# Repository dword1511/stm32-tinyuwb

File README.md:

# Tiny, Ultra-low-power UWB Localization Tag

This is a UWB localization tag based on Decawave `DWM1000` module and STMicro `STM32L031F6P6` ultra-low-power MCU.
The average power consumption is less than 5 mW in 6.8 Mbps mode (10 Hz update rate).

The tag has a built-in `LTC3588-1` energy harvester. WARNING: do not use `LTC3588-2`, their functionalities are very different!
The harvester can be left unpopulated and bypassed by connecting +3V3 directly to an external power source,
and then disabling the power-good logic in the source code.

## General Build Instructions

You will need the following packages (Debian/Ubuntu):

* build-essential
* gcc-arm-none-eabi
* git
* stlink-tools
* gdb-multiarch

You will have to flash and debug via the SWD test-points. Fine air-wire soldering skill required.

This project uses `libopencm3`. It will be automatically checked out during the building process.
To build the firmware, run `make`. To flash it, connect the board to a ST-Link, and then run `make flash`.
Alternatively, you can use `openocd` and any SWD debugger you fancy.

## Publication

This project was part of the following work. Please kindly consider citing the paper as shown:

```
@inproceedings{Capttery,
 author = {Zhang, Chi and Kumar, Sidharth and Bharadia, Dinesh},
 title = {{Capttery: Scalable Battery-like Room-level Wireless Power}},
 booktitle = {Proc. of ACM MobiSys},
 year = {2019},
}
```

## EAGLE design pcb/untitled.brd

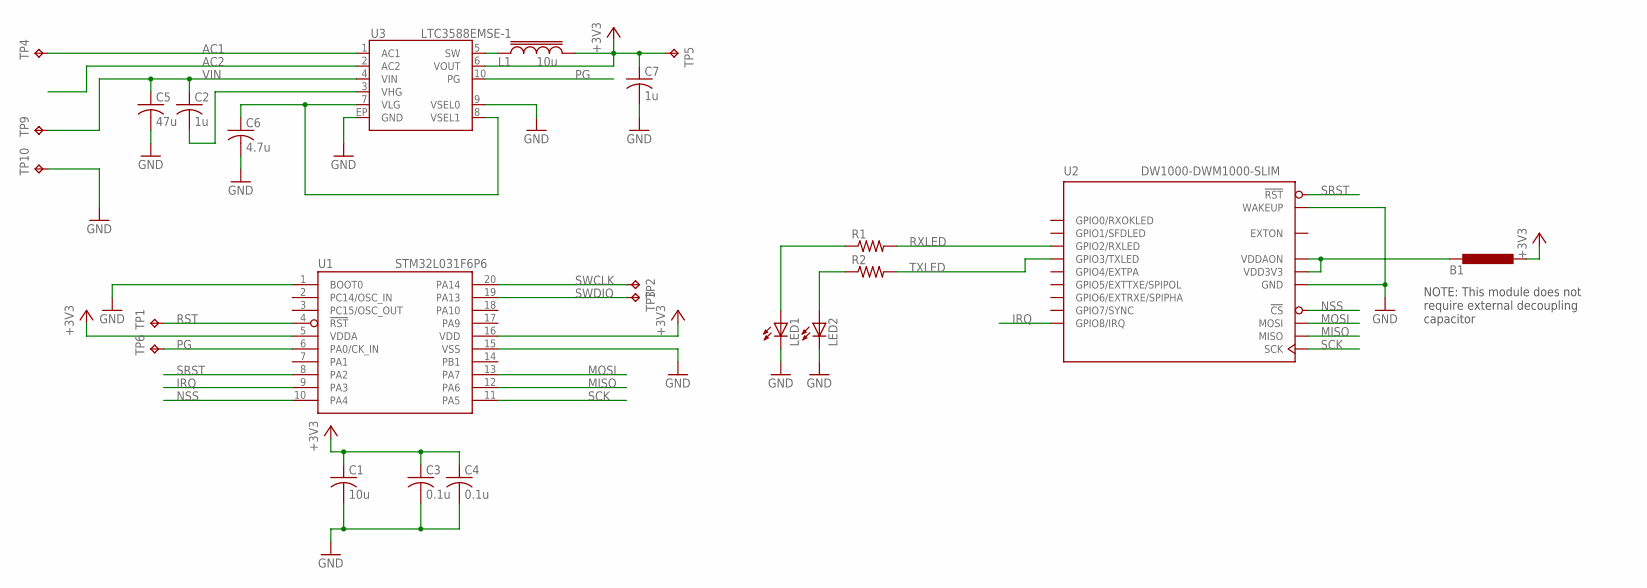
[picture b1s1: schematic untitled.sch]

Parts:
B1: BEAD-0603; 0603
C1: 10u; C0603
C2, C7: 1u; C0603
C3, C4: 0.1u; C0402
C5: 47u; C1206
C6: 4.7u; C0603
L1: 10u; 1008
LED1, LED2: LEDSML0603; SML0603
R1, R2: R-US_R0402; R0402
TP1, TP2, TP3, TP4, TP5, TP6, TP9, TP10: TPB1,27; B1,27
U1: STM32L031F6P6; TSSOP-20
U2: DW1000-DWM1000-SLIM
U3: LTC3588EMSE-1; MSOP-10-3X3-EP

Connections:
+3V3: B1.2, C1.1, C3.1, C4.1, C7.1, L1.2, TP5.TP, U1.5 (VDDA), U1.16 (VDD), U3.6 (VOUT)
AC1: TP4.TP, U3.1 (AC1)
AC2: U3.2 (AC2)
GND: C1.2, C3.2, C4.2, C5.2, C6.2, C7.2, LED1.C, LED2.C, TP10.TP, U1.1 (BOOT0), U1.15 (VSS), U2.2 (WAKEUP), U2.8 (GND), U2.16 (GND), U2.21 (GND), U2.23 (GND), U2.24 (GND), U3.9 (VSEL0), U3.EP (GND)
IRQ: U1.9 (PA3), U2.22 (GPIO8/IRQ)
MISO: U1.12 (PA6), U2.19 (MISO)
MOSI: U1.13 (PA7), U2.18 (MOSI)
unnamed: LED2.A, R2.1
unnamed: LED1.A, R1.1
unnamed: L1.1, U3.5 (SW)
unnamed: B1.1, U2.5 (VDDAON), U2.6 (VDD3V3), U2.7 (VDD3V3)
unnamed: C2.2, U3.3 (VHG)
unnamed: C6.1, U3.7 (VLG), U3.8 (VSEL1)
NSS: U1.10 (PA4), U2.17 (!CS)
PG: TP6.TP, U1.6 (PA0/CK_IN), U3.10 (PG)
RST: TP1.TP, U1.4 (!RST!)
RXLED: R1.2, U2.13 (GPIO2/RXLED)
SCK: U1.11 (PA5), U2.20 (SCK)
SRST: U1.8 (PA2), U2.3 (!RST)
SWCLK: TP2.TP, U1.20 (PA14)
SWDIO: TP3.TP, U1.19 (PA13)
TXLED: R2.2, U2.12 (GPIO3/TXLED)
VIN: C2.1, C5.1, TP9.TP, U3.4 (VIN)

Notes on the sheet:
NOTE: This module does not require external decoupling capacitor

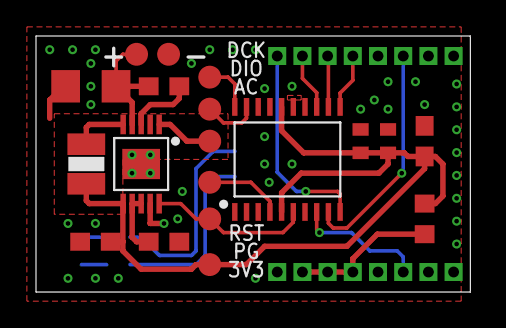
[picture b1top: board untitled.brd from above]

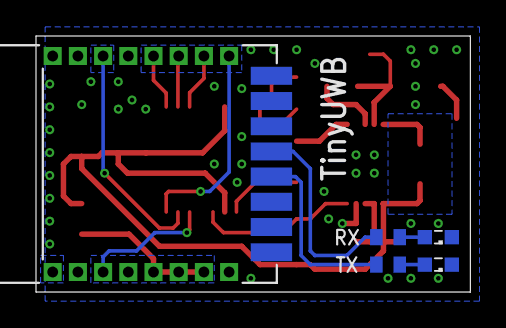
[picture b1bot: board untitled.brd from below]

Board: 2 copper layers, 24.1 x 14.2 mm, 24 parts (5 on the bottom side), 22 nets.

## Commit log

2018-11-07 init
2018-11-08 shrinking
2018-11-08 cleaning in progress
2018-11-08 cleaning up, now single-precision only
2018-11-08 done instance_tag.c
2018-11-08 instance_common.c done
2018-11-08 deep sleep tested
2018-11-08 hardware nss and system simplification
2018-11-09 7.5mw, prepared for clock gating
2018-11-09 working dvfs, 5mw
2018-11-09 add tool for profiling bss usage
2018-11-09 size opt
2018-11-09 add dep for ld script
2018-11-29 minor adjustment
2018-12-11 halfway fix startup bug
2018-12-11 currently startup consumes 500uC
2019-06-10 add doc
2019-06-10 remove loop optimizations as some gcc packages do not support it
